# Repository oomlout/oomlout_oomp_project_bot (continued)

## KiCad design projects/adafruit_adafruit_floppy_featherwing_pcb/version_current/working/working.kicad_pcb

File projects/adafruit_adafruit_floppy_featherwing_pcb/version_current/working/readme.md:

# OOMP Project  
## Adafruit_Floppy_FeatherWing_PCB  by adafruit  
  
oomp key: oomp_projects_flat_adafruit_adafruit_floppy_featherwing_pcb  
(snippet of original readme)  
  
-- Adafruit Floppy FeatherWing with 34-Pin IDC Connector PCB  
  
<a href="http://www.adafruit.com/products/5679"><br/>  
Click here to purchase one from the Adafruit shop</a>  
  
PCB files for the Adafruit Floppy FeatherWing with 34-Pin IDC Connector.   
  
Format is EagleCAD schematic and board layout  
* https://www.adafruit.com/product/5679  
  
--- Description  
  
Relive the days when storage was counted out in kilo-bytes not giga-bytes, using the Adafruit Floppy FeatherWing on a Feather board - perfect for interfacing with 34-Pin IDC Connector floppy drives that were ubiquitous on PC's. This 'Wing has level shifting and a ready-to-plug connector that works with 3.5" or 5.25" floppy disks for reading or writing!  
  
Floppy disks have an interesting data transfer method where raw bit transitions are measured and converted to data. This data streams pretty fast from the disk drive so you'll want to use a fast microcontroller that has large SRAM storage and ideally, a peripheral to DMA the data signal. For that reason we only have this FeatherWing working with the Feather M4 or Feather RP2040. ESP32, ATmega, nRF52, etc have not been ported to our support library!  
  
Floppy disk drives require 5V power and logic. For the logic level shifting, we have a small boost converter on the 'Wing that will give 5V logic levels out the 34-pin connector. It will also shift the incoming signals down to a Feather-safe 3.3V.  
  
For floppy driver powering you will li  
  full source readme at [readme_src.md](readme_src.md)  
  
source repo at: [https://github.com/adafruit/Adafruit_Floppy_FeatherWing_PCB](https://github.com/adafruit/Adafruit_Floppy_FeatherWing_PCB)  
## Board  

## Schematic  

[schematic pdf](working_schematic.pdf)  
## Images

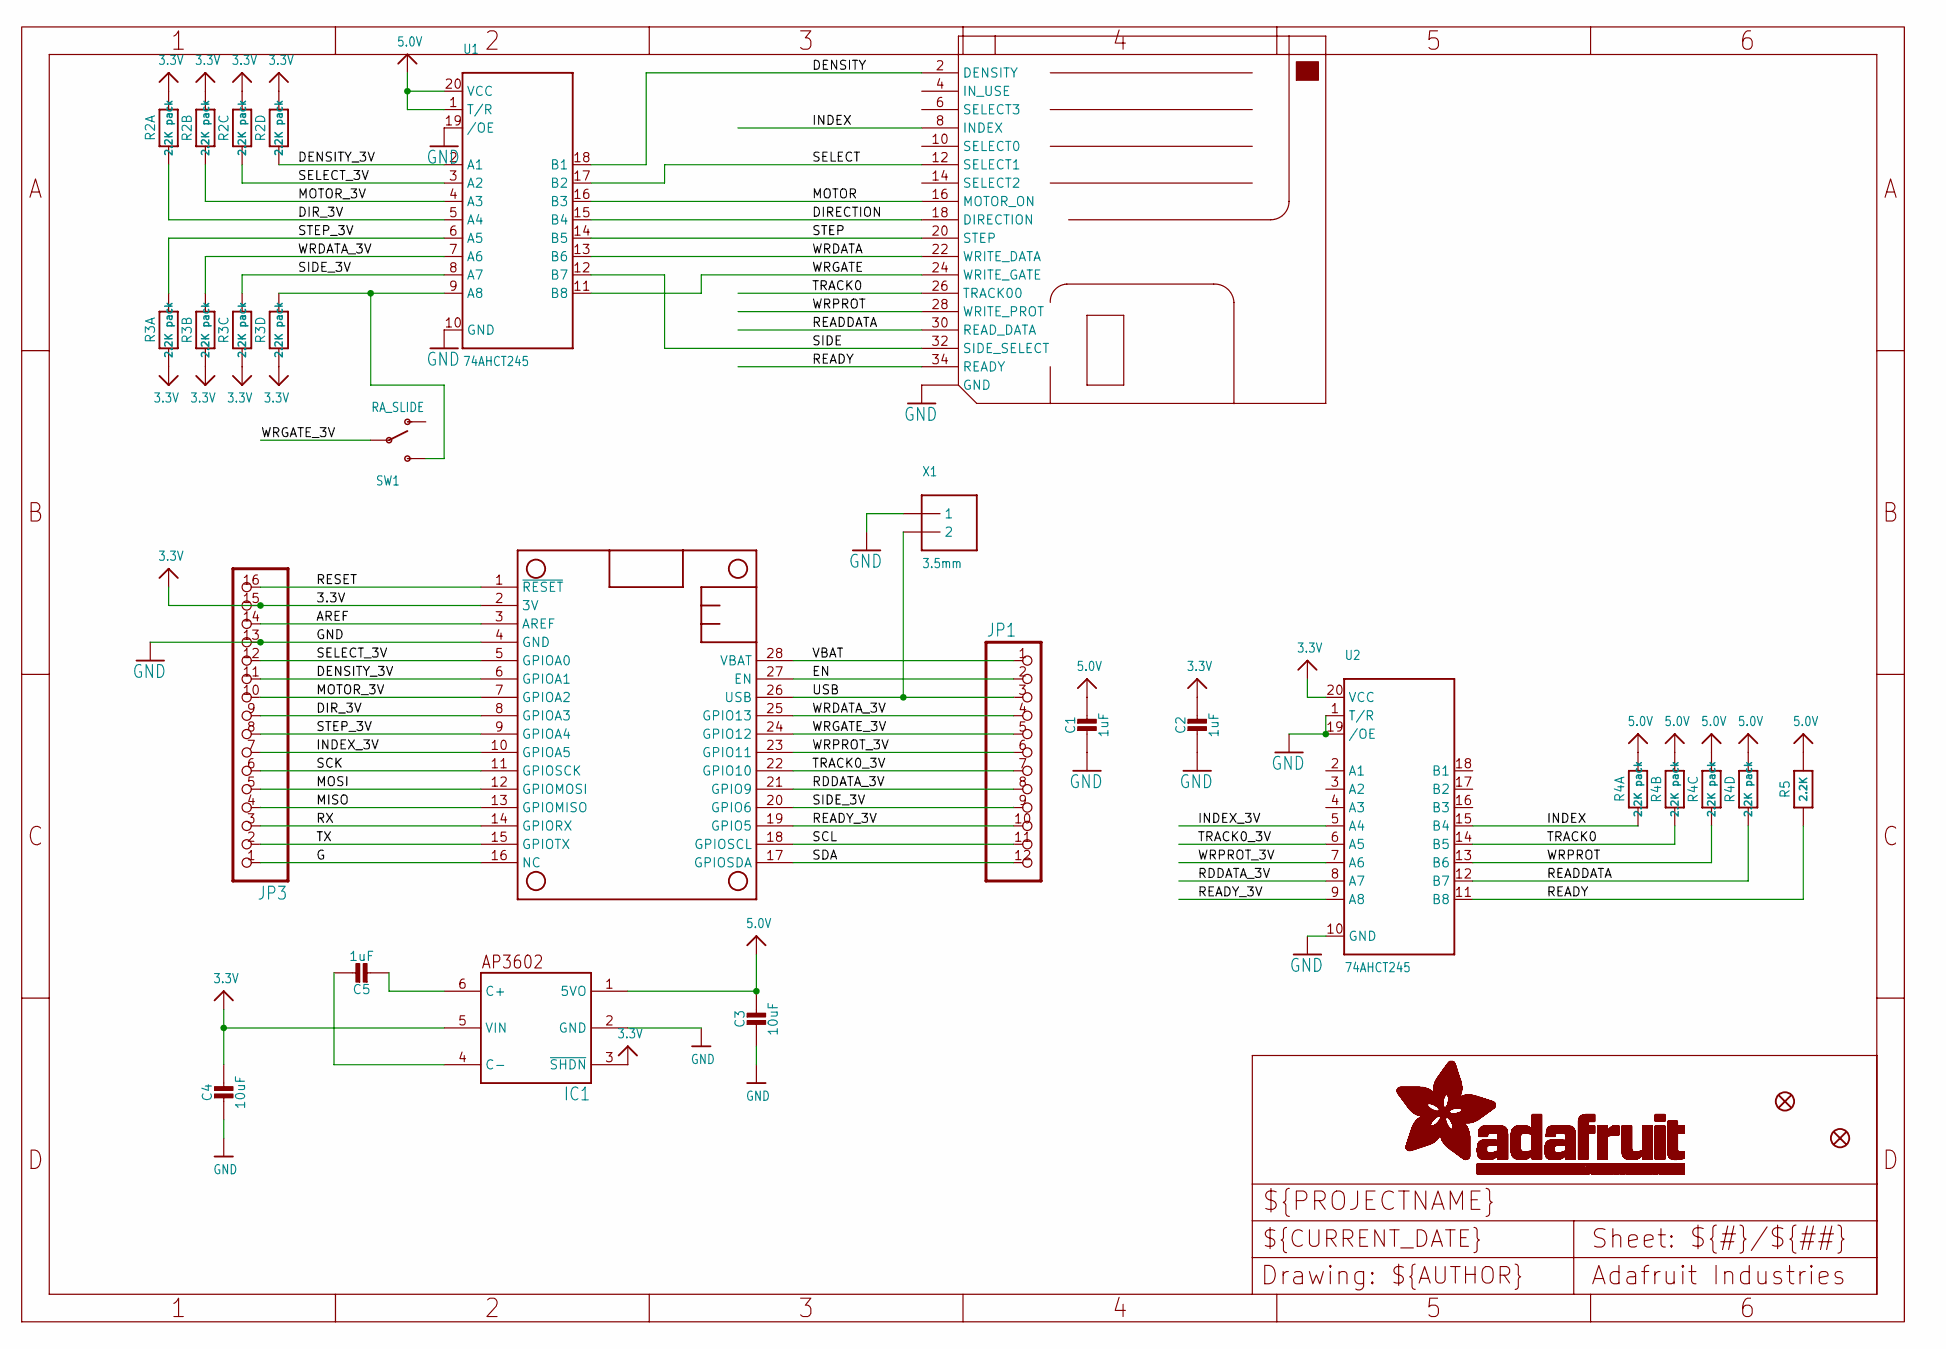
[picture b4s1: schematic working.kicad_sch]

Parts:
C1, C2, C5: 1uF; 0603-NO
C3, C4: 10uF; 0805-NO
FDD1: FLOPPY_IDC_SMT; 2X17_FLOPPY_SMTIDC
FID1, FID2: FIDUCIAL_1MM
IC1: AP3602; SOT23-6
JP1: HEADER-1X12; 1X12_ROUND
JP3: HEADER-1X16ROUND; 1X16_ROUND
MS1: FEATHERWING
R2, R3, R4: 2.2K pack; RESPACK_4X0603
R5: 2.2K; 0603-NO
SW1: RA_SLIDE; SPDT_SMT_SSSS811101
U1, U2: 74AHCT245; SSOP20
X1: 3.5mm; TERMBLOCK_1X2-3.5MM

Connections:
3.3V: C2.1, C4.1, IC1.3 (~SHDN), IC1.5 (VIN), JP3.15, MS1.2 (3V), R2.5 (2), R2.6 (2), R2.7 (2), R2.8 (2), R3.1, R3.2 (1), R3.3 (1), R3.4 (1), U2.20 (VCC)
5.0V: C1.1, C3.1, IC1.1 (5VO), R4.5 (2), R4.6 (2), R4.7 (2), R4.8 (2), R5.2, U1.1 (T/R), U1.20 (VCC)
AREF: JP3.14, MS1.3 (AREF)
DENSITY: FDD1.2 (DENSITY), U1.18 (B1)
DENSITY_3V: JP3.11, MS1.6 (GPIOA1), R2.4 (1), U1.2 (A1)
DIRECTION: FDD1.18 (DIRECTION), U1.15 (B4)
DIR_3V: JP3.9, MS1.8 (GPIOA3), R2.1, U1.5 (A4)
EN: JP1.2, MS1.27 (EN)
G: JP3.1, MS1.16 (NC)
GND: C1.2, C2.2, C3.2, C4.2, FDD1.1 (GND), FDD1.3 (GND), FDD1.5 (GND), FDD1.7 (GND), FDD1.9 (GND), FDD1.11 (GND), FDD1.13 (GND), FDD1.15 (GND), FDD1.17 (GND), FDD1.19 (GND), FDD1.21 (GND), FDD1.23 (GND), FDD1.25 (GND), FDD1.27 (GND), FDD1.29 (GND), FDD1.31 (GND), FDD1.33 (GND), IC1.2 (GND), JP3.13, MS1.4 (GND), U1.10 (GND), U1.19 (/OE), U2.1 (T/R), U2.10 (GND), U2.19 (/OE), X1.1
INDEX: FDD1.8 (INDEX), R4.1, U2.15 (B4)
INDEX_3V: JP3.7, MS1.10 (GPIOA5), U2.5 (A4)
MISO: JP3.4, MS1.13 (GPIOMISO)
MOSI: JP3.5, MS1.12 (GPIOMOSI)
MOTOR: FDD1.16 (MOTOR_ON), U1.16 (B3)
MOTOR_3V: JP3.10, MS1.7 (GPIOA2), R2.2 (1), U1.4 (A3)
unnamed: R3.5 (2), SW1.C (S), U1.9 (A8)
unnamed: C5.2, IC1.6 (C+)
unnamed: C5.1, IC1.4 (C-)
RDDATA_3V: JP1.8, MS1.21 (GPIO9), U2.8 (A7)
READDATA: FDD1.30 (READ_DATA), R4.4 (1), U2.12 (B7)
READY: FDD1.34 (READY), R5.1, U2.11 (B8)
READY_3V: JP1.10, MS1.19 (GPIO5), U2.9 (A8)
RESET: JP3.16, MS1.1 (~RESET)
RX: JP3.3, MS1.14 (GPIORX)
SCK: JP3.6, MS1.11 (GPIOSCK)
SCL: JP1.11, MS1.18 (GPIOSCL)
SDA: JP1.12, MS1.17 (GPIOSDA)
SELECT: FDD1.12 (SELECT1), U1.17 (B2)
SELECT_3V: JP3.12, MS1.5 (GPIOA0), R2.3 (1), U1.3 (A2)
SIDE: FDD1.32 (SIDE_SELECT), U1.12 (B7)
SIDE_3V: JP1.9, MS1.20 (GPIO6), R3.6 (2), U1.8 (A7)
STEP: FDD1.20 (STEP), U1.14 (B5)
STEP_3V: JP3.8, MS1.9 (GPIOA4), R3.8 (2), U1.6 (A5)
TRACK0: FDD1.26 (TRACK00), R4.2 (1), U2.14 (B5)
TRACK0_3V: JP1.7, MS1.22 (GPIO10), U2.6 (A5)
TX: JP3.2, MS1.15 (GPIOTX)
USB: JP1.3, MS1.26 (USB), X1.2
VBAT: JP1.1, MS1.28 (VBAT)
WRDATA: FDD1.22 (WRITE_DATA), U1.13 (B6)
WRDATA_3V: JP1.4, MS1.25 (GPIO13), R3.7 (2), U1.7 (A6)
WRGATE: FDD1.24 (WRITE_GATE), U1.11 (B8)
WRGATE_3V: JP1.5, MS1.24 (GPIO12), SW1.B
WRPROT: FDD1.28 (WRITE_PROT), R4.3 (1), U2.13 (B6)
WRPROT_3V: JP1.6, MS1.23 (GPIO11), U2.7 (A6)

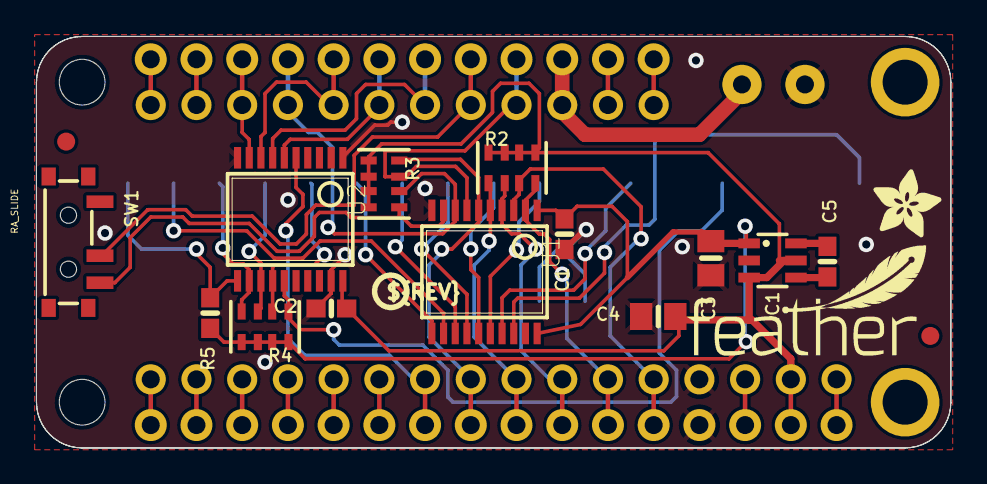
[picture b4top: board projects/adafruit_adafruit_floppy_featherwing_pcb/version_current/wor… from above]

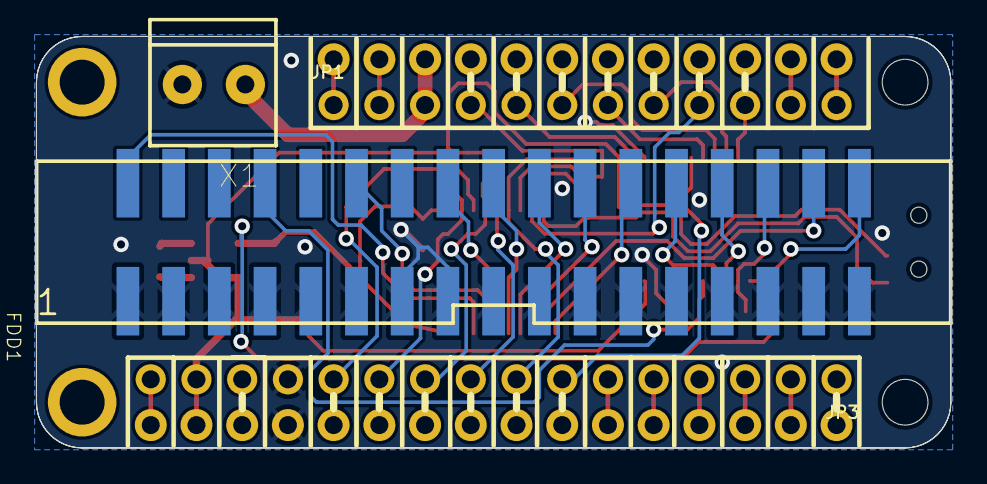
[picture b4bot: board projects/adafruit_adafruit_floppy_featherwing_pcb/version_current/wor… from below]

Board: 2 copper layers, 50.8 x 22.9 mm, 59 parts (26 on the bottom side), 45 nets.

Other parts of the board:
PLABEL0: PLABEL0
PLABEL1: PLABEL1
PLABEL2: PLABEL2
PLABEL3: PLABEL3
PLABEL4: PLABEL4
PLABEL5: PLABEL5
PLABEL6: PLABEL6
PLABEL7: PLABEL7
PLABEL8: PLABEL8
PLABEL9: PLABEL9
PLABEL10: PLABEL10
PLABEL11: PLABEL11
PLABEL12: PLABEL12
PLABEL13: PLABEL13
PLABEL14: PLABEL14
PLABEL15: PLABEL15
PLABEL16: PLABEL16
PLABEL17: PLABEL17
PLABEL18: PLABEL18
PLABEL19: PLABEL19
PLABEL20: PLABEL20
PLABEL21: PLABEL21
PLABEL22: PLABEL22
PLABEL23: PLABEL23
PLABEL24: PLABEL24
PLABEL25: PLABEL25
PLABEL26: PLABEL26
PLABEL27: PLABEL27
PLABEL28: PLABEL28
PLABEL29: PLABEL29
PLABEL30: PLABEL30
PLABEL31: PLABEL31
PLABEL32: PLABEL32
PLABEL33: PLABEL33
PLABEL34: PLABEL34
PLABEL35: PLABEL35
U$26: PCBFEAT-REV-040
U$27: FEATHERLOGO_SMALL
U$28: ADAFRUIT_3.5MM

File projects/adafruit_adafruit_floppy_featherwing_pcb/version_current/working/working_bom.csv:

Row,Description,Part,References,Value,Footprint,Quantity Per PCB,Status,Datasheet
1,,CAP_CERAMIC0603_NO,C1 C2 C5,1uF,0603-NO,3, ,
2,,CAP_CERAMIC0805-NOOUTLINE,C3 C4,10uF,0805-NO,2, ,
3,,FLOPPY_IDC_SMT,FDD1,FLOPPY_IDC_SMT,2X17_FLOPPY_SMTIDC,1, ,
4,,AP3602,IC1,AP3602,SOT23-6,1, ,
5,,HEADER-1X12,JP1,HEADER-1X12,1X12_ROUND,1, ,
6,,HEADER-1X16ROUND,JP3,HEADER-1X16ROUND,1X16_ROUND,1, ,
7,,FEATHERWING,MS1,FEATHERWING,FEATHERWING,1, ,
8,,RESISTOR_4PACK,R2 R3 R4,2.2K pack,RESPACK_4X0603,3, ,
9,,RESISTOR_0603_NOOUT,R5,2.2K,0603-NO,1, ,
10,,SWITCH_SPDT,SW1,RA_SLIDE,SPDT_SMT_SSSS811101,1, ,
11,,74LCX245_SSOP20,U1 U2,74AHCT245,SSOP20,2, ,
12,,TERMBLOCK_1X2_3.5MM,X1,3.5mm,TERMBLOCK_1X2-3.5MM,1, ,





Project info:
Schematic:,working
Variant:,default
Revision:,
Date:,2023-08-02_17-08-33
KiCad Version:,7.0.6-7.0.6~ubuntu22.04.1
Statistics:
Component Groups:,12
Component Count:,18 (0 SMD/ 0 THT)
Fitted Components:,18 (0 SMD/ 0 THT)
Number of PCBs:,1
Total Components:,18

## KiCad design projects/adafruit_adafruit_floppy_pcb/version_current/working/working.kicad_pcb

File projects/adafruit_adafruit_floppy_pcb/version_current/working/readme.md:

# OOMP Project  
## Adafruit_Floppy_PCB  by adafruit  
  
oomp key: oomp_projects_flat_adafruit_adafruit_floppy_pcb  
(snippet of original readme)  
  
- Adafruit_Floppy_PCB  
PCB files for flippy floppys  
  
Untested (as of now) - probably wont work yet  
  
  full source readme at [readme_src.md](readme_src.md)  
  
source repo at: [https://github.com/adafruit/Adafruit_Floppy_PCB](https://github.com/adafruit/Adafruit_Floppy_PCB)  
## Board  

## Schematic  

[schematic pdf](working_schematic.pdf)  
## Images

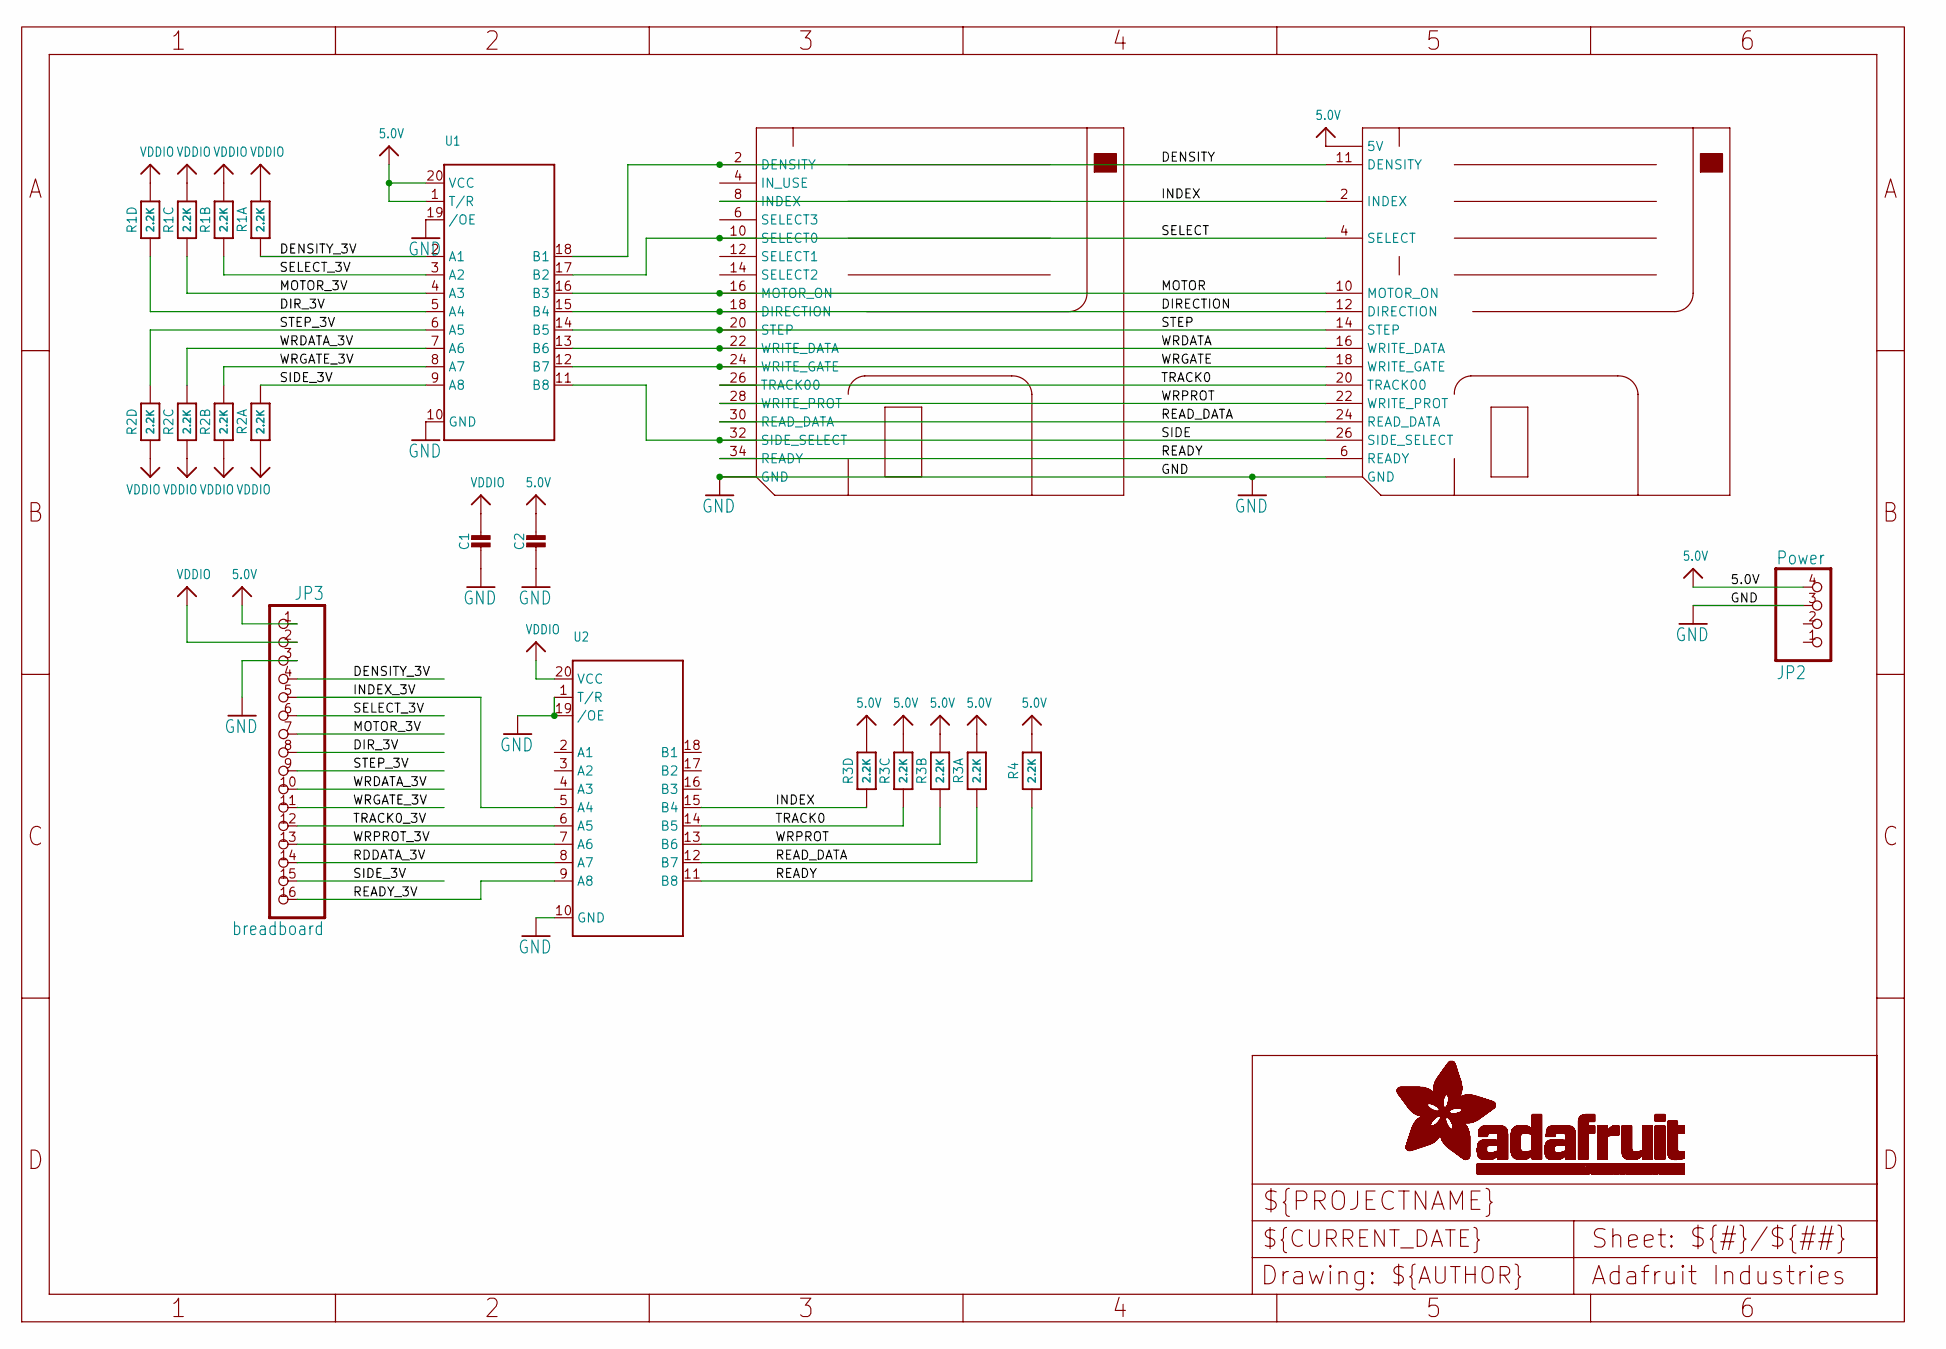
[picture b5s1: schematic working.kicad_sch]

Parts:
C1, C2: CAP_CERAMIC0805-NOOUTLINE; 0805-NO
FDD1: FLOPPY_IDC_SHROUDED; 2X17_FLOPPY_IDC
FDD2: FLOPPY_FPC; FPC_26P_1MM
JP2: Power; 1X04_90
JP3: breadboard; 1X16
R1, R2, R3: 2.2K; RESPACK_4X0603
R4: 2.2K; 0603-NO
U1, U2: 74LCX245; TSSOP20

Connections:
5.0V: C2.1, FDD2.1 (5V), FDD2.3 (5V), FDD2.5 (5V), JP2.4, JP3.1, R3.5 (2), R3.6 (2), R3.7 (2), R3.8 (2), R4.2, U1.1 (T/R), U1.20 (VCC)
DENSITY: FDD1.2 (DENSITY), FDD2.11 (DENSITY), U1.18 (B1)
DENSITY_3V: JP3.4, R1.1, U1.2 (A1)
DIRECTION: FDD1.18 (DIRECTION), FDD2.12 (DIRECTION), U1.15 (B4)
DIR_3V: JP3.8, R1.4 (1), U1.5 (A4)
GND: C1.2, C2.2, FDD1.1 (GND), FDD1.3 (GND), FDD1.5 (GND), FDD1.7 (GND), FDD1.9 (GND), FDD1.11 (GND), FDD1.13 (GND), FDD1.15 (GND), FDD1.17 (GND), FDD1.19 (GND), FDD1.21 (GND), FDD1.23 (GND), FDD1.25 (GND), FDD1.27 (GND), FDD1.29 (GND), FDD1.31 (GND), FDD1.33 (GND), FDD2.15 (GND), FDD2.17 (GND), FDD2.19 (GND), FDD2.21 (GND), FDD2.23 (GND), FDD2.25 (GND), FDD2.M1 (GND), FDD2.M2 (GND), JP2.3, JP3.3, U1.10 (GND), U1.19 (/OE), U2.1 (T/R), U2.10 (GND), U2.19 (/OE)
INDEX: FDD1.8 (INDEX), FDD2.2 (INDEX), R3.4 (1), U2.15 (B4)
INDEX_3V: JP3.5, U2.5 (A4)
MOTOR: FDD1.16 (MOTOR_ON), FDD2.10 (MOTOR_ON), U1.16 (B3)
MOTOR_3V: JP3.7, R1.3 (1), U1.4 (A3)
RDDATA_3V: JP3.14, U2.8 (A7)
READY: FDD1.34 (READY), FDD2.6 (READY), R4.1, U2.11 (B8)
READY_3V: JP3.16, U2.9 (A8)
READ_DATA: FDD1.30 (READ_DATA), FDD2.24 (READ_DATA), R3.1, U2.12 (B7)
SELECT: FDD1.10 (SELECT0), FDD2.4 (SELECT), U1.17 (B2)
SELECT_3V: JP3.6, R1.2 (1), U1.3 (A2)
SIDE: FDD1.32 (SIDE_SELECT), FDD2.26 (SIDE_SELECT), U1.11 (B8)
SIDE_3V: JP3.15, R2.8 (2), U1.9 (A8)
STEP: FDD1.20 (STEP), FDD2.14 (STEP), U1.14 (B5)
STEP_3V: JP3.9, R2.5 (2), U1.6 (A5)
TRACK0: FDD1.26 (TRACK00), FDD2.20 (TRACK00), R3.3 (1), U2.14 (B5)
TRACK0_3V: JP3.12, U2.6 (A5)
VDDIO: C1.1, JP3.2, R1.5 (2), R1.6 (2), R1.7 (2), R1.8 (2), R2.1, R2.2 (1), R2.3 (1), R2.4 (1), U2.20 (VCC)
WRDATA: FDD1.22 (WRITE_DATA), FDD2.16 (WRITE_DATA), U1.13 (B6)
WRDATA_3V: JP3.10, R2.6 (2), U1.7 (A6)
WRGATE: FDD1.24 (WRITE_GATE), FDD2.18 (WRITE_GATE), U1.12 (B7)
WRGATE_3V: JP3.11, R2.7 (2), U1.8 (A7)
WRPROT: FDD1.28 (WRITE_PROT), FDD2.22 (WRITE_PROT), R3.2 (1), U2.13 (B6)
WRPROT_3V: JP3.13, U2.7 (A6)

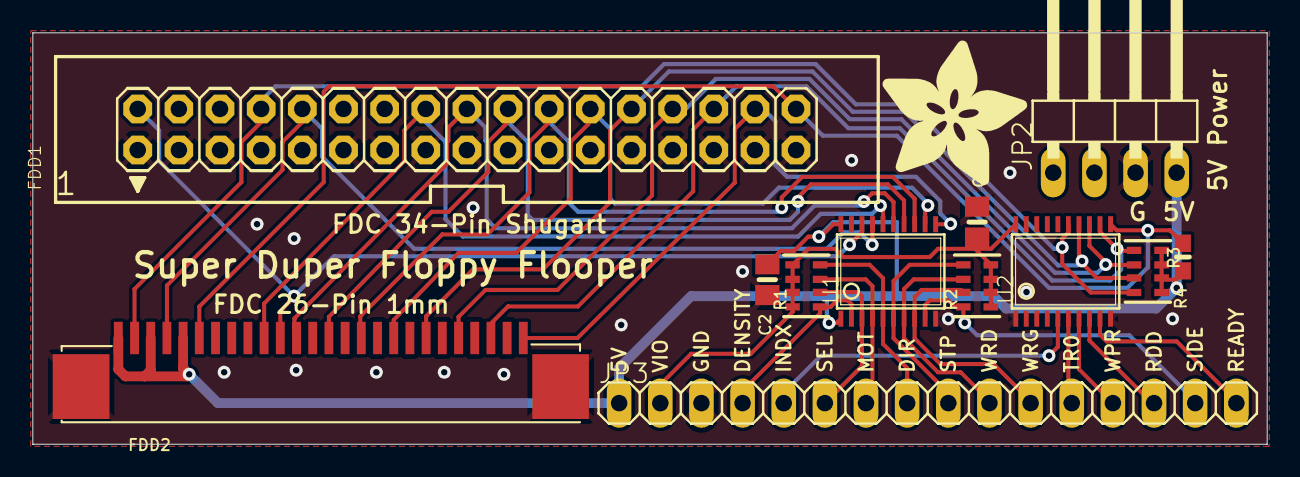
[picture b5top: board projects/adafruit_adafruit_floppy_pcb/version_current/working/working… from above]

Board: 2 copper layers, 76.2 x 25.4 mm, 13 parts (0 on the bottom side), 29 nets.

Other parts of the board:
U$23: ADAFRUIT_9MM

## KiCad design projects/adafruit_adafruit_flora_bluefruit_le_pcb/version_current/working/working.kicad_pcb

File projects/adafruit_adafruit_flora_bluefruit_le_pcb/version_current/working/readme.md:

# Adafruit-Flora-Bluefruit-LE-PCB by adafruit  
This is a harvested standardized copy of a project from github.  
The original project can be found at:  
https://github.com/adafruit/Adafruit-Flora-Bluefruit-LE-PCB  
Please consult that link for additional, details, files, and license information.  
Note: It was auto harvested and if the original repo had more than one board file or anything out of the ordinary the files here are likely not representative.

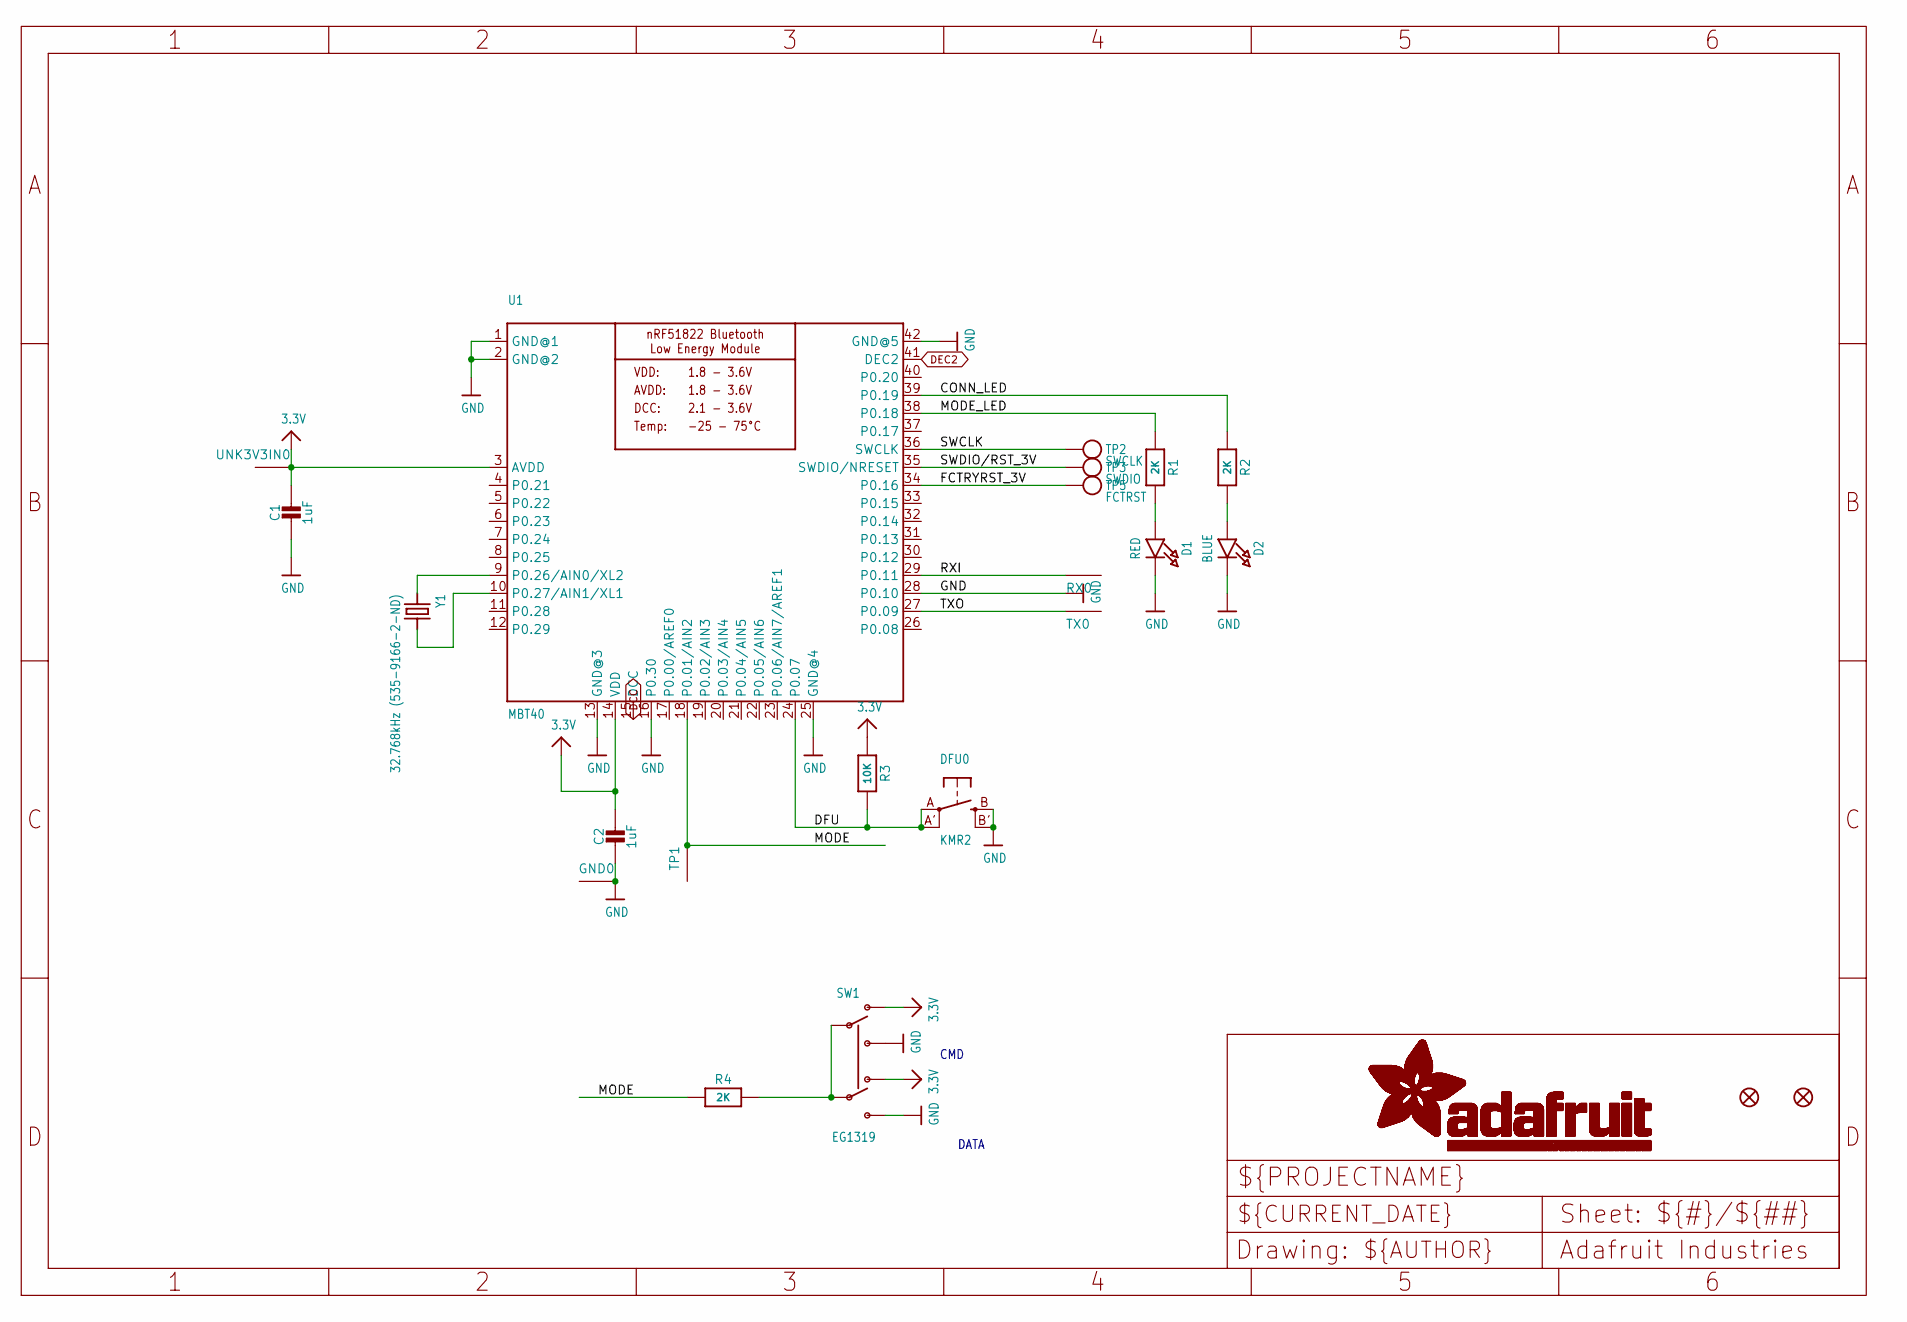
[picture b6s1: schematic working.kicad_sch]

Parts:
C1, C2: 1uF; 0805-NO
D1: RED; CHIPLED_0805_NOOUTLINE
D2: BLUE; CHIPLED_0805_NOOUTLINE
DFU0: KMR2; BTN_KMR2_4.6X2.8
FID1, FID2: FIDUCIAL""; FIDUCIAL_1MM
GND0: SEWTAP-2.0IN; SEWINGTAP_2.0
R1, R2, R4: 2K; 0805-NO
R3: 10K; 0805-NO
RX0: SEWTAP-2.0IN; SEWINGTAP_2.0
SW1: EG1319; EG1390
TP1: SEWTAP-2.0IN; SEWINGTAP_2.0
TP2: SWCLK; PAD-1.5X2.0
TP3: SWDIO; PAD-1.5X2.0
TP5: FCTRST; PAD-1.5X2.0
TX0: SEWTAP-2.0IN; SEWINGTAP_2.0
U1: MBT40; BLE_MODULE_RAYTAC_MDBT40
UNK3V3IN0: SEWTAP-2.0IN; SEWINGTAP_2.0
Y1: 32.768kHz (535-9166-2-ND); CRYSTAL_CYL_2X6MM_SMT

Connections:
3.3V: C1.1, C2.1, R3.1, SW1.O1, SW1.O2, U1.3 (AVDD), U1.14 (VDD), UNK3V3IN0.P$1
CONN_LED: R2.1, U1.39 (P0.19)
DCC: U1.15 (DCC)
DEC2: U1.41 (DEC2)
DFU: DFU0.A, DFU0.A' (P1), R3.2, U1.24 (P0.07)
FCTRYRST_3V: TP5.P$1, U1.34 (P0.16)
GND: C1.2, C2.2, D1.C, D2.C, DFU0.B (S), DFU0.B' (S1), GND0.P$1, SW1.S1, SW1.S2, U1.1 (GND@1), U1.2 (GND@2), U1.13 (GND@3), U1.16 (P0.30), U1.25 (GND@4), U1.28 (P0.10), U1.42 (GND@5)
MODE: R4.1, TP1.P$1, U1.18 (P0.01/AIN2)
MODE_LED: R1.1, U1.38 (P0.18)
unnamed: R4.2, SW1.P1, SW1.P2
unnamed: D1.A, R1.2
unnamed: D2.A, R2.2
unnamed: U1.9 (P0.26/AIN0/XL2), Y1.1
unnamed: U1.10 (P0.27/AIN1/XL1), Y1.2
RXI: RX0.P$1, U1.29 (P0.11)
SWCLK: TP2.P$1, U1.36 (SWCLK)
SWDIO/RST_3V: TP3.P$1, U1.35 (SWDIO/NRESET)
TXO: TX0.P$1, U1.27 (P0.09)

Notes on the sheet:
DATA
CMD

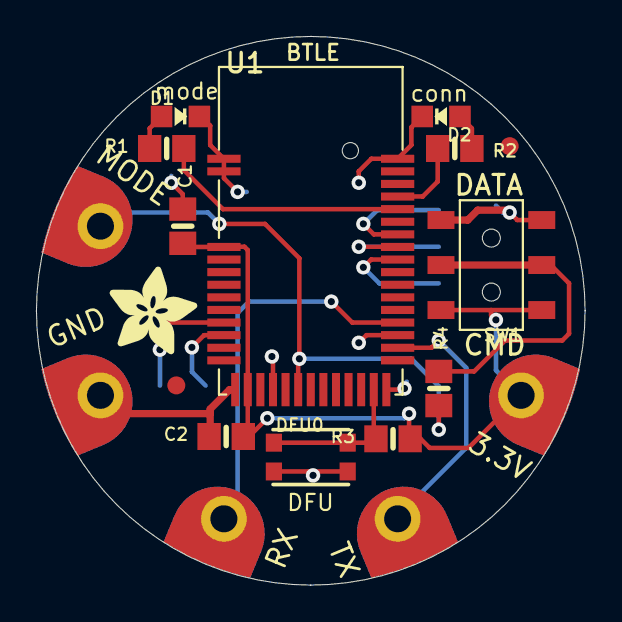
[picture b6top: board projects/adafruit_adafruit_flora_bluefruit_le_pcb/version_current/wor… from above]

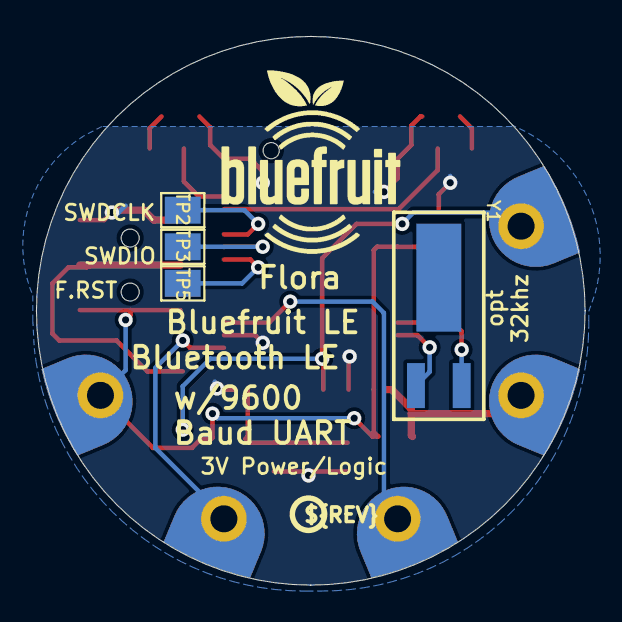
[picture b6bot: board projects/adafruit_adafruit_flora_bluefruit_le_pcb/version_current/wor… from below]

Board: 2 copper layers, 30.5 x 30.5 mm, 26 parts (7 on the bottom side), 16 nets.

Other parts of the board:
U$6: ADAFRUIT_5MM
U$7: FLORASMALL
U$23: BLUEFRUITLOGO_100MM
U$24: PCBFEAT-REV-040
